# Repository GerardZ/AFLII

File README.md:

# AFLII

## A Faster Lcd I2c Interface

### **So what is this ?**

This is a replacement for the PCF8574 LCD-interface board, which is pin but not API compatible.

It is faster and less cpu consuming for the host because the used AtTiny414 takes care of low-level data handling, besides BUSY-flag is used instead of wait-routines which allows for faster and more easy writing the display.

### **And why should i use this ?**

For me this was a getting-to-know the AtTiny414 project, but it also has some advantages above the PCF8574-solution.

Pro\`s:

*   faster, steering the LCD module is off-loaded from the host. Benchmarked @>300 lines/second
*   more efficient by using BUSY instead of wait
*   easy API, in essence just push line number and string over i2c. Uses less memory and cpu on host
*   cheaper (at least @Mouser, a AtTiny814 costs around 55 cents, where a PCF8574 does 120 cents)
*   Backlight dimming !   
*   you could incorporate some custom routines
*   pin free for user
*   you might learn from this :)

Con\`s:

*   the rest of the world uses PCF8574
*   there\`s no ready-build hardware available
*   API differs from the PCF solution

Todo:

*   The WaitBusy should hold I2C communication by clock stretching. We now still need a delay @host side.
*   Better PCB design
*   More & clearer examples

Schema:

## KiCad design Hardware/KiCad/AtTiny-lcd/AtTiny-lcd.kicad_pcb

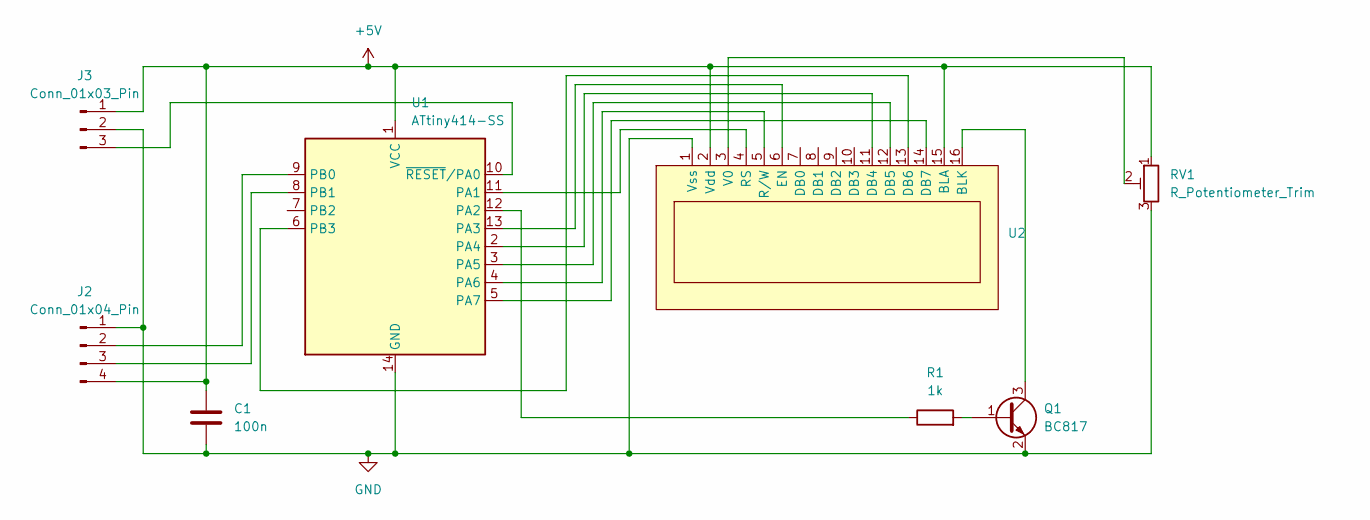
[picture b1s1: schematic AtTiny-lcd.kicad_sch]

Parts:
C1: 100n; C_0805_2012Metric_Pad1.18x1.45mm_HandSolder
J2: Conn_01x04_Pin; PinHeader_1x04_P2.54mm_Vertical
J3: Conn_01x03_Pin; PinHeader_1x03_P2.54mm_Vertical
Q1: BC817; SOT-23
R1: 1k; R_0805_2012Metric_Pad1.20x1.40mm_HandSolder
RV1: R_Potentiometer_Trim; Potentiometer_SMD_EBay_10k
U1: ATtiny414-SS; SOIC-14_3.9x8.7mm_P1.27mm
U2: LCD2008

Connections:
+5V: C1.1, J2.4, J3.1, RV1.1, U1.1 (VCC), U2.2 (Vdd), U2.15 (BLA)
GND: C1.2, J2.1, J3.2, Q1.2 (E), RV1.3, U1.14 (GND), U2.1 (Vss)
unnamed: J2.2, U1.9 (PB0)
unnamed: J2.3, U1.8 (PB1)
unnamed: J3.3, U1.10 (~RESET/PA0)
unnamed: Q1.1 (B), R1.2
unnamed: Q1.3 (C), U2.16 (BLK)
unnamed: U1.11 (PA1), U2.4 (RS)
unnamed: R1.1, U1.12 (PA2)
unnamed: U1.13 (PA3), U2.6 (EN)
unnamed: U1.2 (PA4), U2.11 (DB4)
unnamed: U1.3 (PA5), U2.12 (DB5)
unnamed: U1.4 (PA6), U2.5 (R/W)
unnamed: U1.5 (PA7), U2.14 (DB7)
unnamed: U1.6 (PB3), U2.13 (DB6)
unnamed: RV1.2, U2.3 (V0)

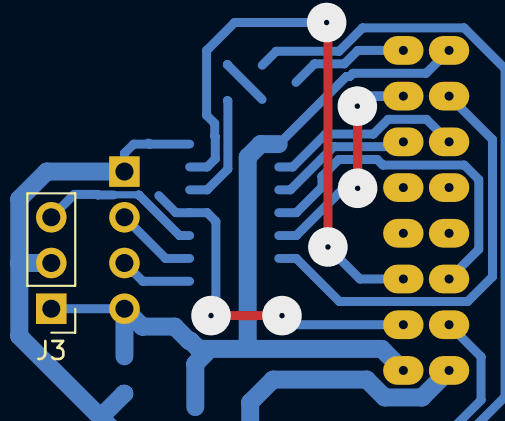
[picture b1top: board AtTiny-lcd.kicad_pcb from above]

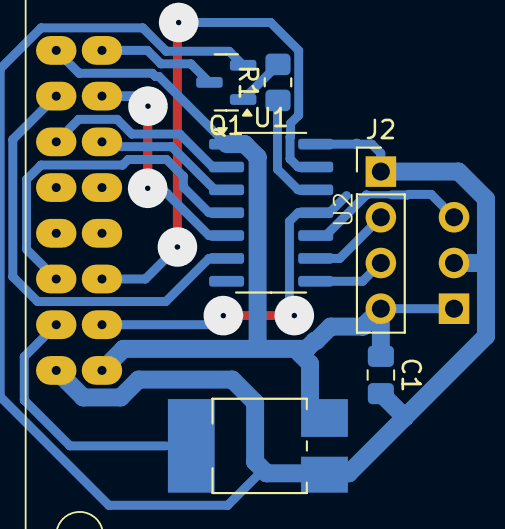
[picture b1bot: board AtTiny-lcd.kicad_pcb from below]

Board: 2 copper layers, 8 parts (7 on the bottom side), 16 nets.

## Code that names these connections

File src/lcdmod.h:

#pragma once

#include <Arduino.h>

using UCommand = uint8_t;
enum : UCommand
{
  NOP,                // NOP also used to indicate no command has been received
  LINE1,              // set cursor line 1, subsequenting bytes write that line
  LINE2,              // same line 2
  LINE3,              // same line 3
  LINE4,              // same line 4
  RAW,
  CLEAR,              // clear lcd
  BL_ON,              // backlight on
  BL_OFF,             // backlight off
  BL_SET,             // backlight set dim 0-255 in next byte, 1 subsequent byte expected
  SET_CUSTOM_CHAR0,   // define cusom char0, 8 subsequent bytes expected
  SET_CUSTOM_CHAR1,
  SET_CUSTOM_CHAR2,
  SET_CUSTOM_CHAR3,
  SET_CUSTOM_CHAR4,
  SET_CUSTOM_CHAR5,
  SET_CUSTOM_CHAR6,
  SET_CUSTOM_CHAR7,
};

#define LCD_D4 PIN_PA4
#define LCD_D5 PIN_PA5
#define LCD_D6 PIN_PB3 //PIN_PA2
#define LCD_D7 PIN_PA7
#define LCD_RS PIN_PA1
#define LCD_RW PIN_A6
#define LCD_EN PIN_PA3
#define LCD_BL PIN_PA2 //PIN_PB3

#define LCD_SETCGRAMADDR 0x40

#define LCD_CLEAR 0x01           // from https://dawes.wordpress.com/2010/01/05/hd44780-instruction-set/
#define LCD_HOME  0x02
#define LCD_Mode_8Bit 0x33
#define LCD_Mode_4Bit 0x32
#define LCD_Mode_2Line_5x7 0x28
#define LCD_On_CursorOff 0x0C
#define LCD_On_CursorSteady 0x0E
#define LCD_On_CursorBlink 0x0F


#define LCD_SetCursorPosition 0x80

#define LCD_line0_addr 0x00
#define LCD_line1_addr 0x40
#define LCD_line2_addr 0x14
#define LCD_line3_addr 0x54


void LCD_Init();
void LCD_Write(char *str, uint8_t line = 1, uint8_t index = 0);
void LCD_Write(uint8_t chr, uint8_t line = 1, uint8_t index = 0);
void LCD_Write(uint8_t *charArray, uint8_t length, uint8_t line = 1, uint8_t index = 0);
void LCD_Send(uint8_t data);
void LCD_Clear();
void LCD_SendCommand(uint8_t data);
void LCD_SendData(uint8_t data);
void LCD_Backlight(uint8_t value);
void LCD_createChar(uint8_t location, uint8_t charmap[]);
void WaitBusy();
void Pulse_EN();
void LCD_ShortDelay();
void SetBacklightDimInt(uint8_t dimValue);
void SetBacklightDimTimer(uint8_t dimValue);

extern byte Smiley[];
extern byte Heart[];
extern byte Bell[];

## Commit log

2024-04-05 init
2024-04-05 KiCad files added
2024-04-05 cleanup #1
2024-04-21 Cleanup & WaitBusy straightened
2024-07-30 Backlight dimming
2024-07-30 tidy up
2024-07-31 PCB updated
2024-08-01 updated PCB dimming through ISR
2024-08-01 PNG of schema and PCB
